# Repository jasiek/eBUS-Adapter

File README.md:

# eBUS-Adapter
A few designs for an eBUS Adapter taken from the Internet and made into PCBs

## Peter A Henning

## Tony Gröger

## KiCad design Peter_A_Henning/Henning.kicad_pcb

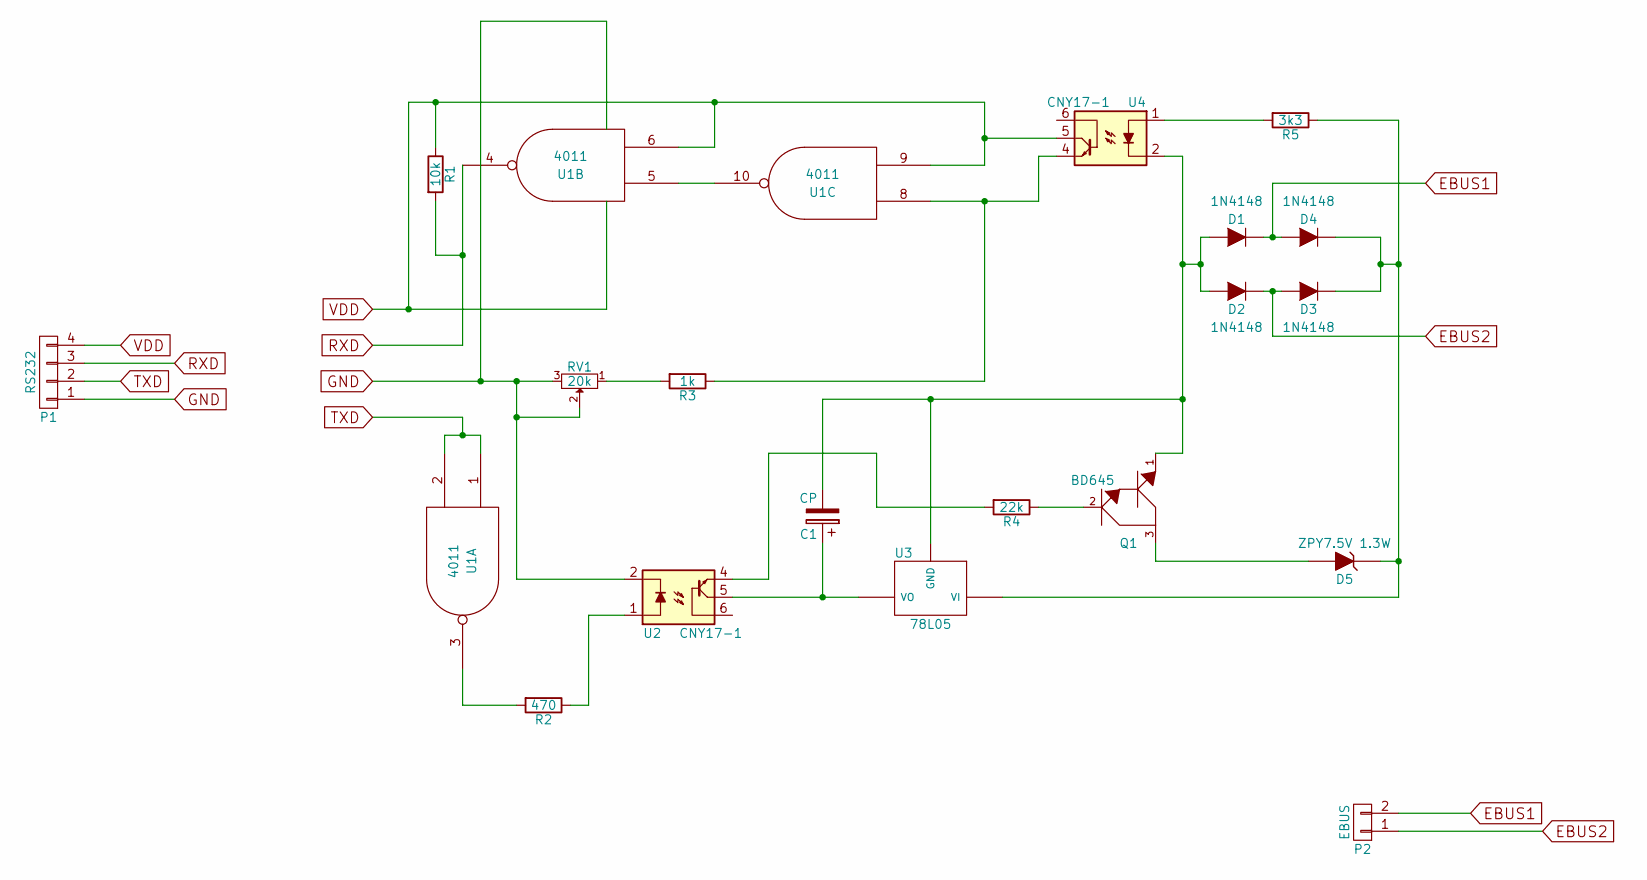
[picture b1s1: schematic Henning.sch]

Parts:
C1: CP; C_Radial_D5_L6_P2.5
D1, D2, D3, D4: 1N4148; Diode_DO-35_SOD27_Horizontal_RM10
D5: ZPY7.5V 1.3W; Diode_DO-35_SOD27_Horizontal_RM10
P1: RS232; Pin_Header_Straight_1x04
P2: EBUS; TerminalBlock_Pheonix_MKDS1.5-2pol
Q1: BD645; TO-220_Neutral123_Vertical
R1: 10k; Resistor_Horizontal_RM10mm
R2: 470; Resistor_Horizontal_RM10mm
R3: 1k; Resistor_Horizontal_RM10mm
R4: 22k; Resistor_Horizontal_RM10mm
R5: 3k3; Resistor_Horizontal_RM10mm
RV1: 20k; Potentiometer_Bourns_3296W_3-8Zoll_Inline_ScrewUp
U1: 4011; DIP-14_W7.62mm
U2, U4: CNY17-1; DIP-6_W7.62mm
U3: 78L05; TO-220_Neutral123_Horizontal

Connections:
EBUS1: D1.1 (K), D4.2 (A), P2.2
EBUS2: D2.1 (K), D3.2 (A), P2.1
GND: P1.1, RV1.2, RV1.3, U1.7 (VSS), U2.2
unnamed: C1.1, U2.5, U3.3 (VO)
unnamed: C1.2, D1.2 (A), D2.2 (A), Q1.1, U3.2 (GND), U4.2
unnamed: D3.1 (K), D4.1 (K), D5.1 (K), R5.1, U3.1 (VI)
unnamed: D5.2 (A), Q1.3
unnamed: Q1.2, R4.1
unnamed: R2.1, U2.1
unnamed: R2.2, U1.3
unnamed: R3.1, U1.8, U4.4
unnamed: R3.2, RV1.1
unnamed: R4.2, U2.4
unnamed: R5.2, U4.1
unnamed: U1.5, U1.10
RXD: P1.3, R1.2, U1.4
TXD: P1.2, U1.1, U1.2
VDD: P1.4, R1.1, U1.6, U1.9, U1.14 (VDD), U4.5

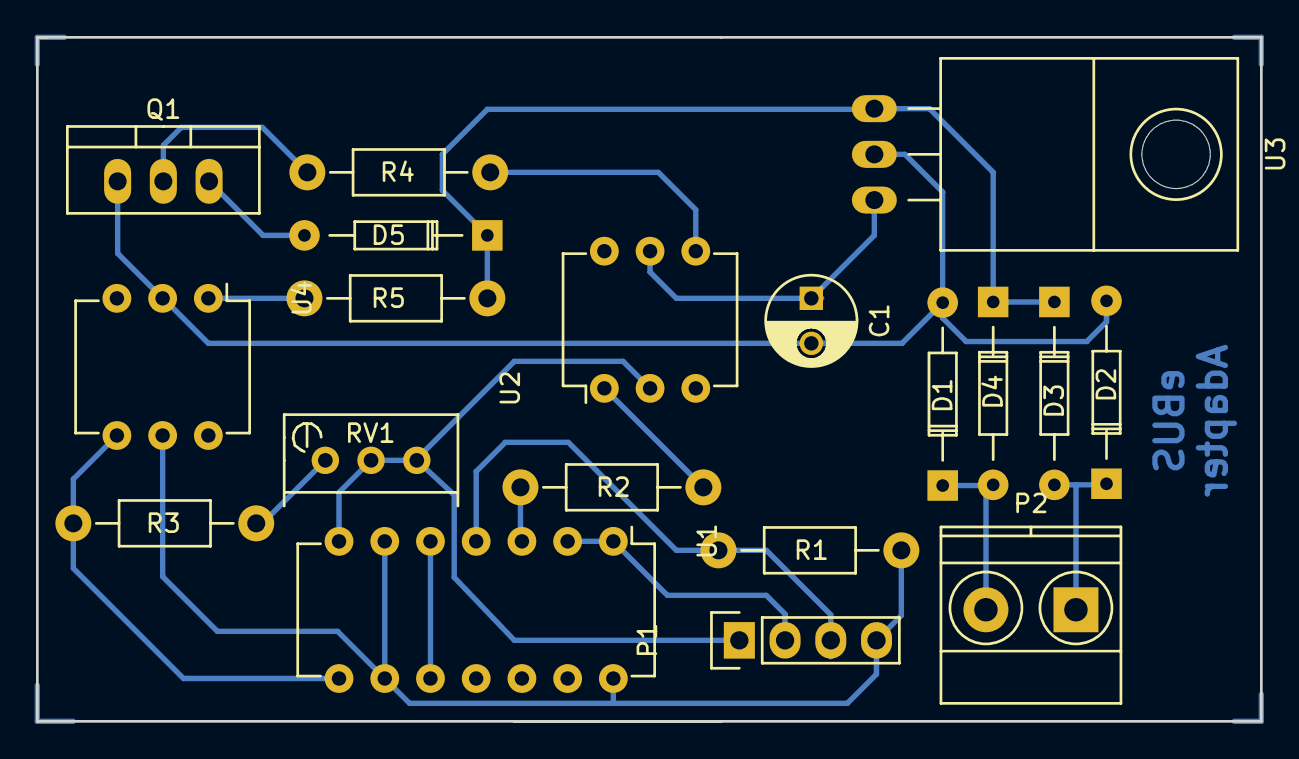
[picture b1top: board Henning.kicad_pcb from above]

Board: 2 copper layers, 68.0 x 38.0 mm, 19 parts (0 on the bottom side), 18 nets.

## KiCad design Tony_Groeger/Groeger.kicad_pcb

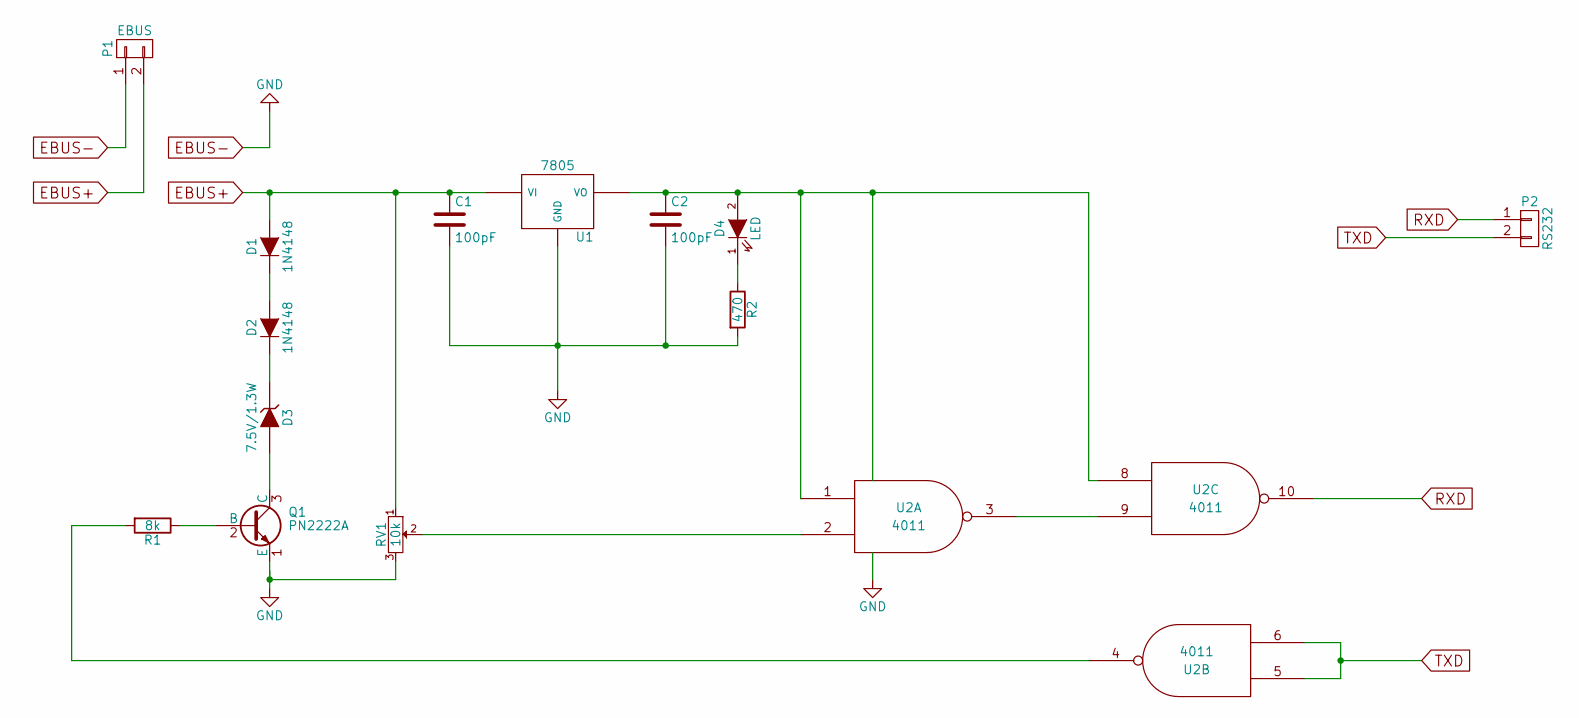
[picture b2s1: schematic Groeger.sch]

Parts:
C1, C2: 100pF; C_Disc_D3_P2.5
D1, D2: 1N4148; Diode_DO-41_SOD81_Horizontal_RM10
D3: 7.5V/1.3W; Diode_DO-41_SOD81_Horizontal_RM10
D4: LED; LED-5MM
P1: EBUS; TerminalBlock_Pheonix_PT-3.5mm_2pol
P2: RS232; Pin_Header_Straight_1x02
Q1: PN2222A; TO-92_Molded_Wide
R1: 8k; Resistor_Horizontal_RM10mm
R2: 470; Resistor_Horizontal_RM10mm
RV1: 10k; Potentiometer_Bourns_3296W_3-8Zoll_Inline_ScrewUp
U1: 7805; TO-92_Molded_Wide
U2: 4011; DIP-14_W7.62mm

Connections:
EBUS+: C1.1, D1.2 (A), P1.2, RV1.1, U1.1 (VI)
EBUS-: C1.2, C2.2, P1.1, Q1.1 (E), R2.2, RV1.3, U1.2 (GND), U2.7 (VSS)
unnamed: D1.1 (K), D2.2 (A)
unnamed: D2.1 (K), D3.1 (K)
unnamed: D3.2 (A), Q1.3 (C)
unnamed: D4.1 (K), R2.1
unnamed: Q1.2 (B), R1.1
unnamed: R1.2, U2.4
unnamed: RV1.2, U2.2
unnamed: U2.3, U2.9
RXD: P2.1, U2.10
TXD: P2.2, U2.5, U2.6
VDD: C2.1, D4.2 (A), U1.3 (VO), U2.1, U2.8, U2.14 (VDD)

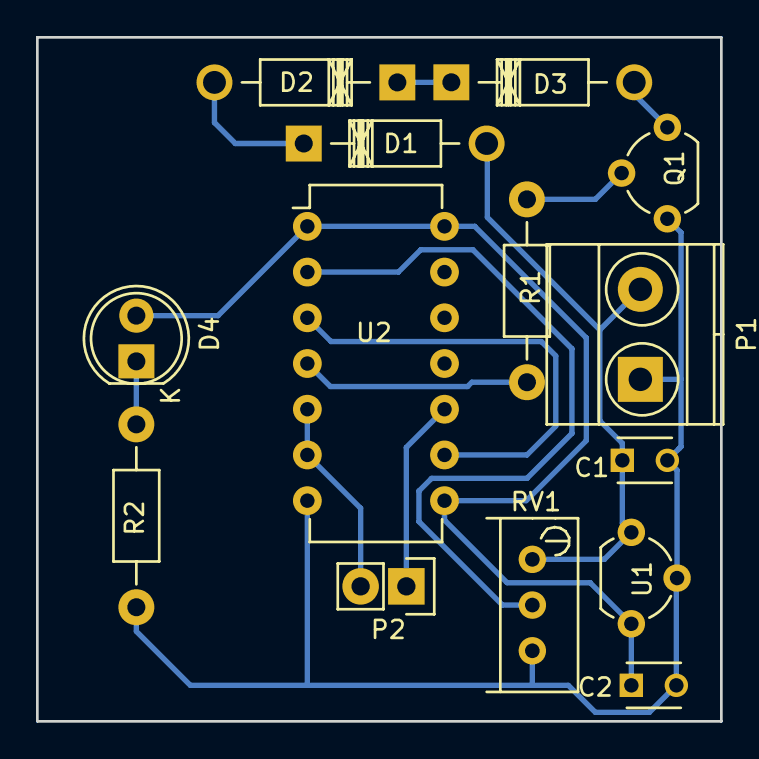
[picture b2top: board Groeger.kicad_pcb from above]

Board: 2 copper layers, 38.0 x 38.0 mm, 14 parts (0 on the bottom side), 13 nets.

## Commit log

2016-09-22 Schematic.
2016-09-22 Design by prof dr Peter A Henning
2016-09-22 PCB generated, but with some errors.
2016-09-23 Fixed PCB
2016-09-23 Quick rename.
2016-09-23 Initial schema by Tony Groeger.
    http://www.mikrocontroller.net/topic/91164
2016-09-23 PCB generated.
2016-09-23 Re-generated Henning's board using a different terminal block.
2016-09-23 Generated gerbers for Henning.
2016-09-23 Generated gerbers for Groeger's design.
2016-09-25 Changed Groeger's PCB terminal block component to something we have on hand.
2016-09-25 Ditto for Henning's design.
2016-09-25 Updated README with schematics.
2016-09-26 Added some text on the copper layer.
2016-09-30 Generated some gerbers.
2016-09-30 Fixed a silly error - reversed some polarities, no wonder this whole thing didn't work.
2016-09-30 Added a LED, regenerated production files.
